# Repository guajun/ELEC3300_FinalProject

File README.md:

# ELEC3300_FinalProject

CAN - 电机

SDIO - sd卡

I2S - 扬声器

CRC 电机驱动信息校验

spi - oled ST7735

adc - 功率

uart - ws2812

uart - 3DConn 

usb hid - 键盘

uart - rs485（硬件流控）

Timer - encoder interface 增量编码器

Timer - PWM 呼吸灯

I2C - 距离传感器 VL53L0X

GPIO - Valve

GPIO - Relay

# ZYD

## 难
spi - oled ST7735

uart - 3DConn

## 一般
uart - ws2812

## 简单
Timer - encoder interface 增量编码器

## 超简单
Timer - PWM 呼吸灯

adc - 功率

GPIO - Valve

GPIO - Relay

# LGY
CAN - 电机

SDIO - sd卡

I2S - 扬声器

CRC 电机驱动信息校验

usb hid - 键盘

uart - rs485（硬件流控）

I2C - 距离传感器 VL53L0X

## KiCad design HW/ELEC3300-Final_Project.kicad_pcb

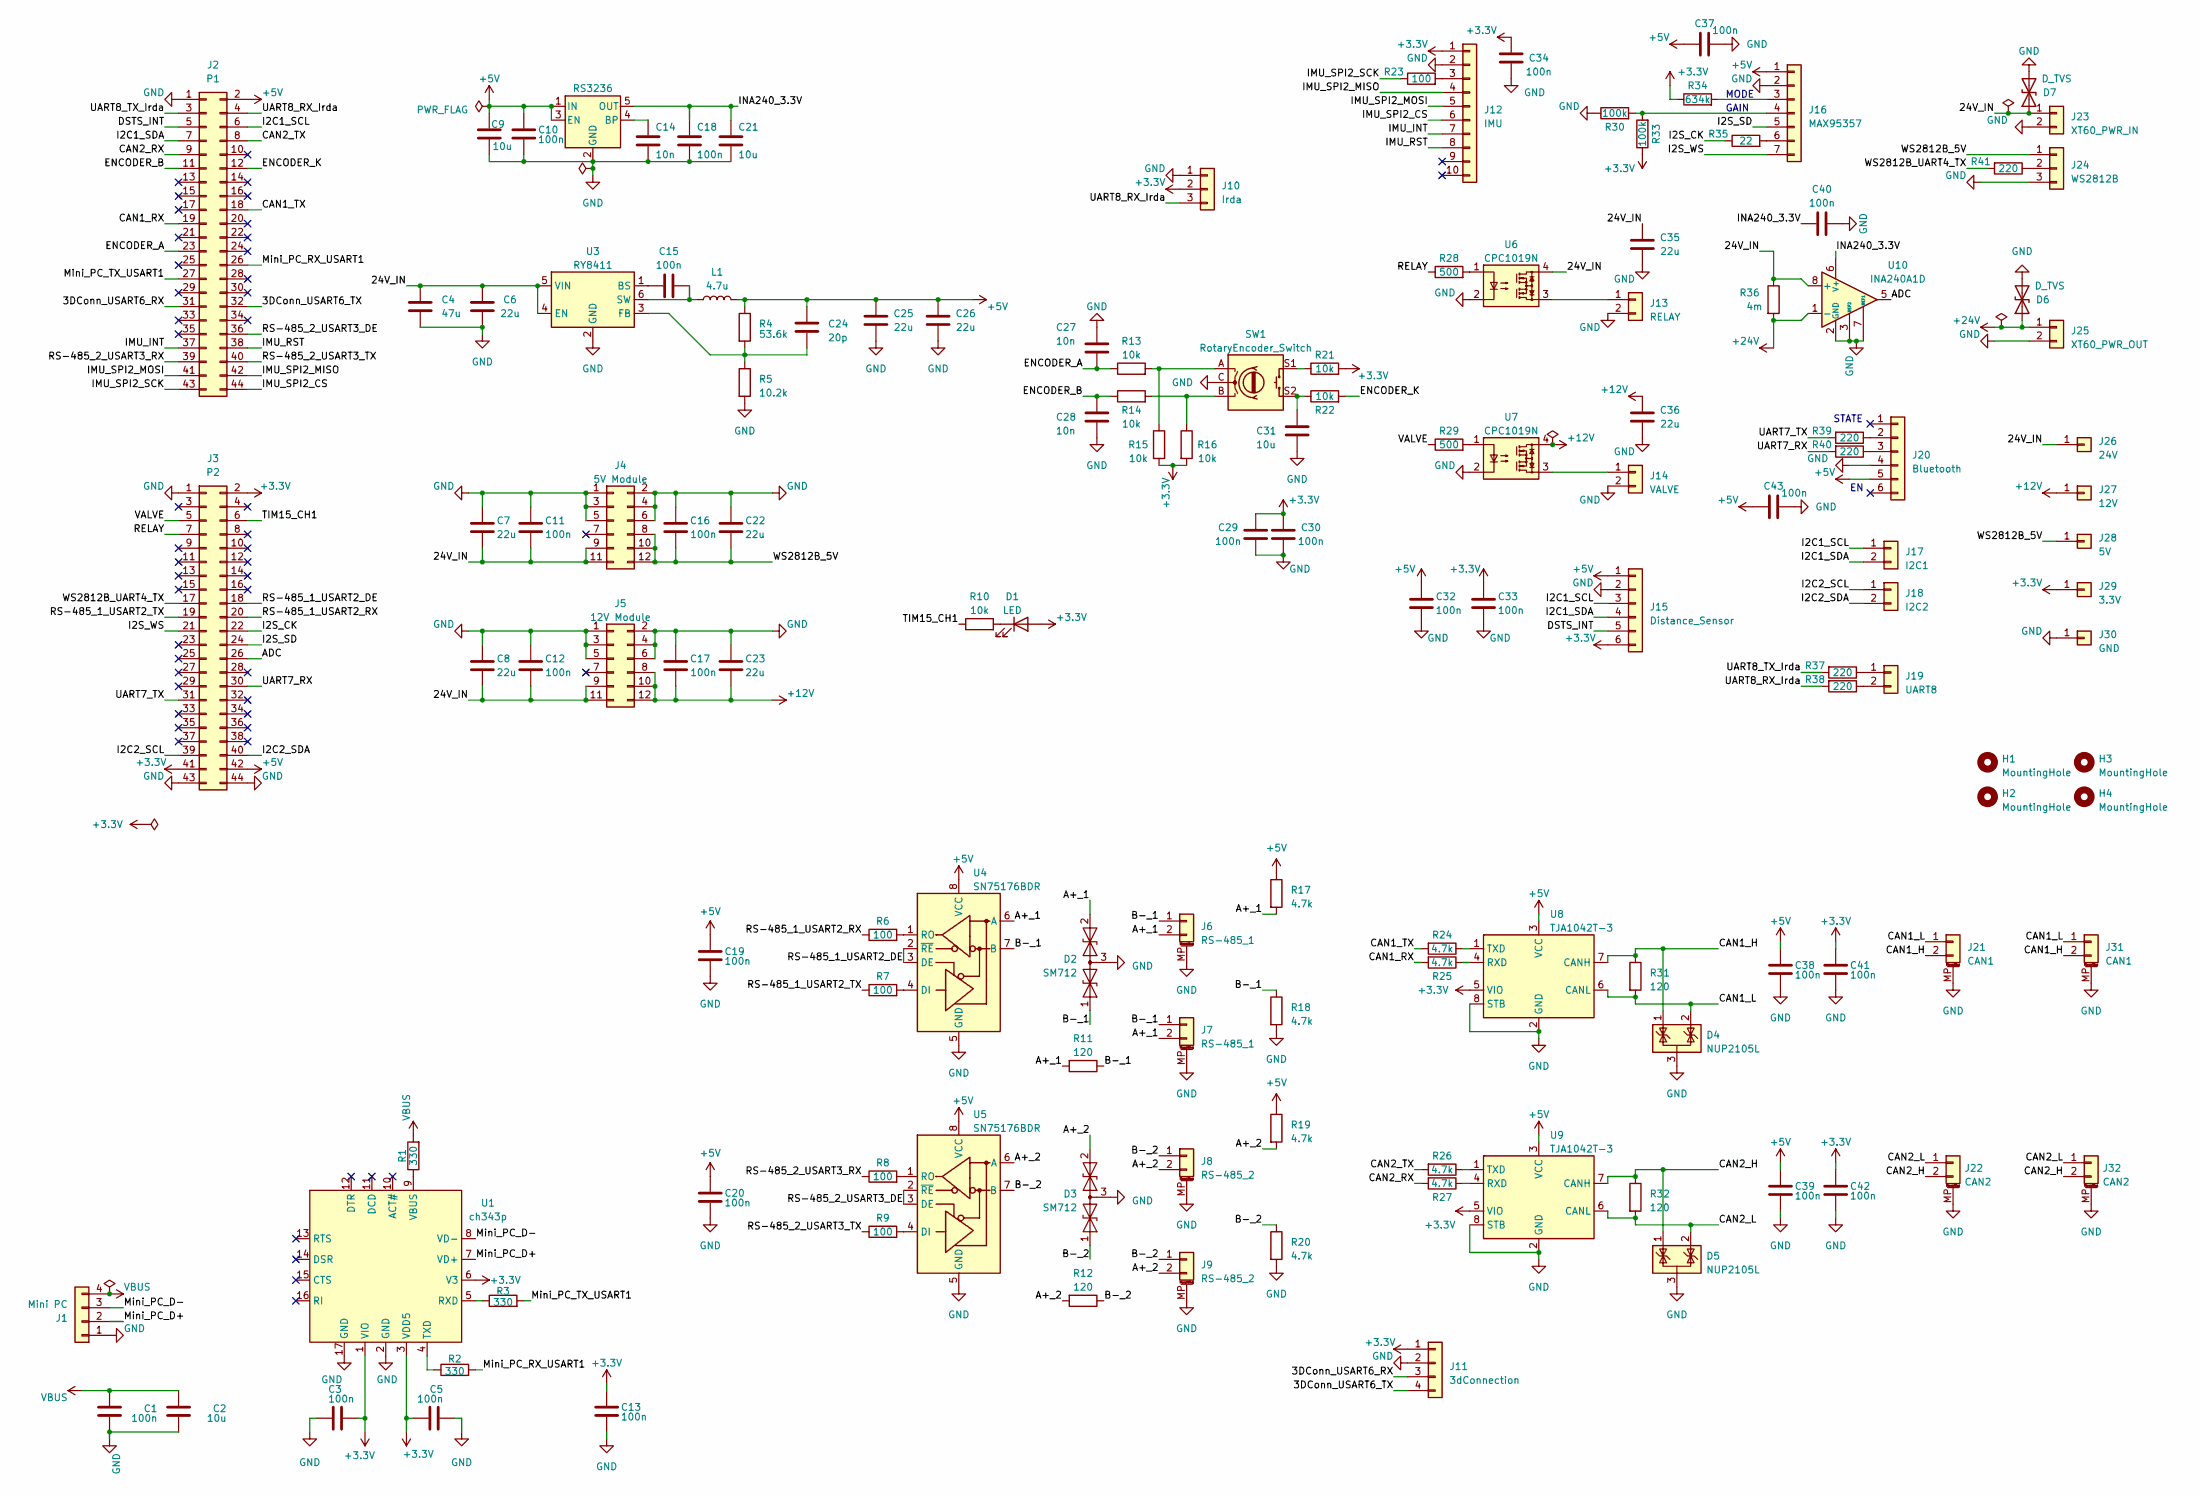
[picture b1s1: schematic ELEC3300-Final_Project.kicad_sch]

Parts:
C1, C3, C5, C10, C11, C12, C13, C15, C16, C17, C18, C19, C20, C29, C30, C32, C33, C34, C37, C38, C39, C40, C41, C42, C43: 100n; C_0603_1608Metric
C2, C9, C21: 10u; C_0805_2012Metric
C4: 47u; C_1206_3216Metric
C6, C7, C8, C22, C23, C25, C26, C35, C36: 22u; C_0805_2012Metric
C14, C27, C28: 10n; C_0603_1608Metric
C24: 20p; C_0603_1608Metric
C31: 10u; C_0603_1608Metric
D1: LED; LED_0603_1608Metric
D2, D3: SM712; SOT-23
D4, D5: NUP2105L; SOT-23
D6, D7: D_TVS; D_SMC
H1, H2, H3, H4: MountingHole; MountingHole_3.2mm_M3_ISO7380_Pad
J1: Mini PC; JST_PH_S4B-PH-K_1x04_P2.00mm_Horizontal
J2: P1; PinSocket_2x22_P2.54mm_Vertical
J3: P2; PinSocket_2x22_P2.54mm_Vertical
J4: 5V Module; 24V Buck
J5: 12V Module; 24V Buck
J6, J7: RS-485_1; JST_GH_SM02B-GHS-TB_1x02-1MP_P1.25mm_Horizontal
J8, J9: RS-485_2; JST_GH_SM02B-GHS-TB_1x02-1MP_P1.25mm_Horizontal
J10: Irda; PinSocket_1x03_P2.54mm_Vertical
J11: 3dConnection; PinHeader_1x04_P2.54mm_Horizontal
J12: IMU; PinSocket_1x10_P2.54mm_Vertical
J13: RELAY; JST_PH_S2B-PH-SM4-TB_1x02-1MP_P2.00mm_Horizontal
J14: VALVE; JST_PH_S2B-PH-SM4-TB_1x02-1MP_P2.00mm_Horizontal
J15: Distance_Sensor; PinSocket_1x06_P2.54mm_Horizontal
J16: MAX95357; PinSocket_1x07_P2.54mm_Vertical
J17: I2C1; PinHeader_1x02_P2.54mm_Vertical
J18: I2C2; PinHeader_1x02_P2.54mm_Vertical
J19: UART8; PinHeader_1x02_P2.54mm_Vertical
J20: Bluetooth; PinSocket_1x06_P2.54mm_Vertical
J21, J31: CAN1; JST_GH_SM02B-GHS-TB_1x02-1MP_P1.25mm_Horizontal
J22, J32: CAN2; JST_GH_SM02B-GHS-TB_1x02-1MP_P1.25mm_Horizontal
J23: XT60_PWR_IN; AMASS_XT60-M_1x02_P7.20mm_Vertical
J24: WS2812B; PinHeader_1x03_P2.54mm_Vertical
J25: XT60_PWR_OUT; AMASS_XT60-F_1x02_P7.20mm_Vertical
J26: 24V; TestPoint_Pad_4.0x4.0mm
J27: 12V; TestPoint_Pad_2.0x2.0mm
J28: 5V; TestPoint_Pad_2.0x2.0mm
J29: 3.3V; TestPoint_Pad_2.0x2.0mm
J30: GND; TestPoint_Pad_4.0x4.0mm
L1: 4.7u; L_Abracon_ASPI-0630LR
R1, R2, R3: 330; R_0603_1608Metric
R4: 53.6k; R_0603_1608Metric
R5: 10.2k; R_0603_1608Metric
R6, R7, R8, R9, R23: 100; R_0603_1608Metric
R10, R13, R14, R15, R16, R21, R22: 10k; R_0603_1608Metric
R11, R12, R31, R32: 120; R_0603_1608Metric
R17, R18, R19, R20, R24, R25, R26, R27: 4.7k; R_0603_1608Metric
R28, R29: 500; R_0603_1608Metric
R30, R33: 100k; R_0603_1608Metric
R34: 634k; R_0603_1608Metric
R35: 22; R_0603_1608Metric
R36: 4m; R_2512_6332Metric
R37, R38, R39, R40, R41: 220; R_0603_1608Metric
SW1: RotaryEncoder_Switch; RotaryEncoder_Alps_EC11E-Switch_Vertical_H20mm
U1: ch343p; CH343P
U2: RS3236; SOT-23-5
U3: RY8411; SOT-23-6
U4, U5: SN75176BDR; SOIC-8_3.9x4.9mm_P1.27mm
U6, U7: CPC1019N; SOP-4_3.8x4.1mm_P2.54mm
U8, U9: TJA1042T-3; SOIC-8_3.9x4.9mm_P1.27mm
U10: INA240A1D; SOIC-8_3.9x4.9mm_P1.27mm

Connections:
+3.3V: C3.1, C5.1, C13.1, C29.2, C30.2, C33.2, C34.2, C41.1, C42.1, D1.2 (A), J3.2, J3.41, J10.2, J11.1, J12.1, J15.6, J29.1, R15.2, R16.2, R21.2, R33.1, R34.1, U1.1 (VIO), U1.3 (VDD5), U1.6 (V3), U8.5 (VIO), U9.5 (VIO)
+5V: C9.1, C10.1, C19.1, C20.1, C24.1, C25.1, C26.1, C32.1, C37.1, C38.1, C39.1, C43.1, J2.2, J3.42, J15.1, J16.1, J20.5, L1.2, R4.1, R17.1, R19.1, U2.1 (IN), U2.3 (EN), U4.8 (VCC), U5.8 (VCC), U8.3 (VCC), U9.3 (VCC)
+12V: C17.2, C23.2, C36.1, J5.8, J5.10, J5.12, J27.1, U7.4
+24V: D6.1 (A1), J25.1, R36.2, U10.1 (-)
/3DConn_USART6_RX: J2.31, J11.3
/3DConn_USART6_TX: J2.32, J11.4
/24V_IN: C4.1, C6.1, C7.2, C8.2, C11.2, C12.2, C35.1, D7.1 (A1), J4.9, J4.11, J5.9, J5.11, J23.1, J26.1, R36.1, U3.4 (EN), U3.5 (VIN), U6.4, U10.8 (+)
/A+_1: D2.2 (A2), J6.2, J7.2, R11.2, R17.2, U4.6 (A)
/A+_2: D3.2 (A2), J8.2, J9.2, R12.2, R19.2, U5.6 (A)
/ADC: J3.26, U10.5
/B-_1: D2.1 (A1), J6.1, J7.1, R11.1, R18.1, U4.7 (B)
/B-_2: D3.1 (A1), J8.1, J9.1, R12.1, R20.1, U5.7 (B)
/CAN1_H: D4.1 (K), J21.2, J31.2, R31.1, U8.7 (CANH)
/CAN1_L: D4.2 (K), J21.1, J31.1, R31.2, U8.6 (CANL)
/CAN1_RX: J2.19, R25.2
/CAN1_TX: J2.18, R24.2
/CAN2_H: D5.1 (K), J22.2, J32.2, R32.1, U9.7 (CANH)
/CAN2_L: D5.2 (K), J22.1, J32.1, R32.2, U9.6 (CANL)
/CAN2_RX: J2.9, R27.2
/CAN2_TX: J2.8, R26.2
/DSTS_INT: J2.5, J15.5
/ENCODER_A: C27.2, J2.23, R13.1
/ENCODER_B: C28.1, J2.11, R14.1
/ENCODER_K: J2.12, R22.2
/I2C1_SCL: J2.6, J15.3, J17.1
/I2C1_SDA: J2.7, J15.4, J17.2
/I2C2_SCL: J3.39, J18.1
/I2C2_SDA: J3.40, J18.2
/I2S_CK: J3.22, R35.1
/I2S_SD: J3.24, J16.5
/I2S_WS: J3.21, J16.7
/IMU_INT: J2.37, J12.7
/IMU_RST: J2.38, J12.8
/IMU_SPI2_CS: J2.44, J12.6
/IMU_SPI2_MISO: J2.42, J12.4
/IMU_SPI2_MOSI: J2.41, J12.5
/IMU_SPI2_SCK: J2.43, R23.1
/INA240_3.3V: C18.1, C21.1, C40.1, U2.5 (OUT), U10.6 (V+)
/Mini_PC_D+: J1.2, U1.7 (VD+)
/Mini_PC_D-: J1.3, U1.8 (VD-)
/Mini_PC_RX_USART1: J2.26, R2.2
/Mini_PC_TX_USART1: J2.27, R3.2
/RELAY: J3.7, R28.1
/RS-485_1_USART2_DE: J3.18, U4.2 (~RE), U4.3 (DE)
/RS-485_1_USART2_RX: J3.20, R6.1
/RS-485_1_USART2_TX: J3.19, R7.1
/RS-485_2_USART3_DE: J2.36, U5.2 (~RE), U5.3 (DE)
/RS-485_2_USART3_RX: J2.39, R8.1
/RS-485_2_USART3_TX: J2.40, R9.1
/TIM15_CH1: J3.6, R10.1
/UART7_RX: J3.30, R40.2
/UART7_TX: J3.31, R39.2
/UART8_RX_Irda: J2.4, J10.3, R38.2
/UART8_TX_Irda: J2.3, R37.2
/VALVE: J3.5, R29.1
/WS2812B_5V: C16.2, C22.2, J4.8, J4.10, J4.12, J24.1, J28.1
/WS2812B_UART4_TX: J3.17, R41.2
GND: C1.2, C2.2, C3.2, C4.2, C5.2, C6.2, C7.1, C8.1, C9.2, C10.2, C11.1, C12.1, C13.2, C14.2, C16.1, C17.1, C18.2, C19.2, C20.2, C21.2, C22.1, C23.1, C25.2, C26.2, C27.1, C28.2, C29.1, C30.1, C31.2, C32.2, C33.1, C34.1, C35.2, C36.2, C37.2, C38.2, C39.2, C40.2, C41.2, C42.2, C43.2, D2.3 (common), D3.3 (common), D4.3 (A), D5.3 (A), D6.2 (A2), D7.2 (A2), J1.1, J2.1, J3.1, J3.43, J3.44, J4.1, J4.2, J4.3, J4.4, J4.5, J4.6, J5.1, J5.2, J5.3, J5.4, J5.5, J5.6, J6.MP (MountPin), J7.MP (MountPin), J8.MP (MountPin), J9.MP (MountPin), J10.1, J11.2, J12.2, J13.2, J14.2, J15.2, J16.2, J20.4, J21.MP (MountPin), J22.MP (MountPin), J23.2, J24.3, J25.2, J30.1, J31.MP (MountPin), J32.MP (MountPin), R5.2, R18.2, R20.2, R30.1, SW1.C, U1.2 (GND), U1.17 (GND), U2.2 (GND), U3.2 (GND), U4.5 (GND), U5.5 (GND), U6.2, U7.2, U8.2 (GND), U8.8 (STB), U9.2 (GND), U9.8 (STB), U10.2 (GND), U10.3 (REF2), U10.4 (GND), U10.7 (REF1)
unnamed: C31.1, R22.1, SW1.S2
unnamed: D1.1 (K), R10.2
unnamed: J12.3, R23.2
unnamed: J13.1, U6.3
unnamed: J14.1, U7.3
unnamed: J16.3, R34.2
unnamed: J16.4, R30.2, R33.2
unnamed: J16.6, R35.2
unnamed: J19.1, R37.1
unnamed: J19.2, R38.1
unnamed: J20.2, R39.1
unnamed: J20.3, R40.1
unnamed: J24.2, R41.1
unnamed: R13.2, R15.1, SW1.A
unnamed: R14.2, R16.1, SW1.B
unnamed: R21.1, SW1.S1
unnamed: R28.2, U6.1
unnamed: R29.2, U7.1
unnamed: R3.1, U1.5 (RXD)
unnamed: R2.1, U1.4 (TXD)
unnamed: R1.1, U1.9 (VBUS)
unnamed: C14.1, U2.4 (BP)
unnamed: C15.1, U3.1 (BS)
unnamed: C24.2, R4.2, R5.1, U3.3 (FB)
unnamed: C15.2, L1.1, U3.6 (SW)
unnamed: R7.2, U4.4 (DI)
unnamed: R6.2, U4.1 (RO)
unnamed: R9.2, U5.4 (DI)
unnamed: R8.2, U5.1 (RO)
unnamed: R25.1, U8.4 (RXD)
unnamed: R24.1, U8.1 (TXD)
unnamed: R27.1, U9.4 (RXD)
unnamed: R26.1, U9.1 (TXD)
VBUS: C1.1, C2.1, J1.4, R1.2

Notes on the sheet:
STATE
MODE
GAIN

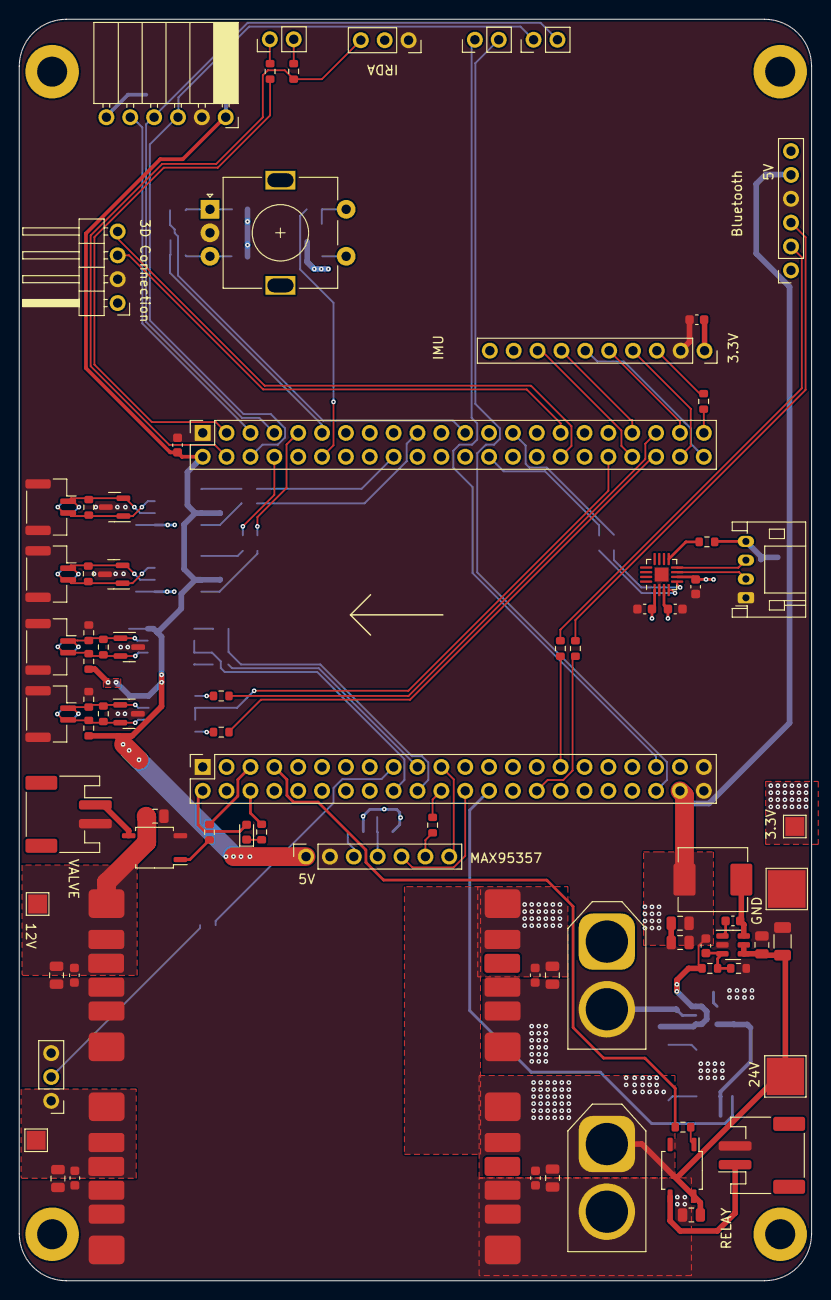
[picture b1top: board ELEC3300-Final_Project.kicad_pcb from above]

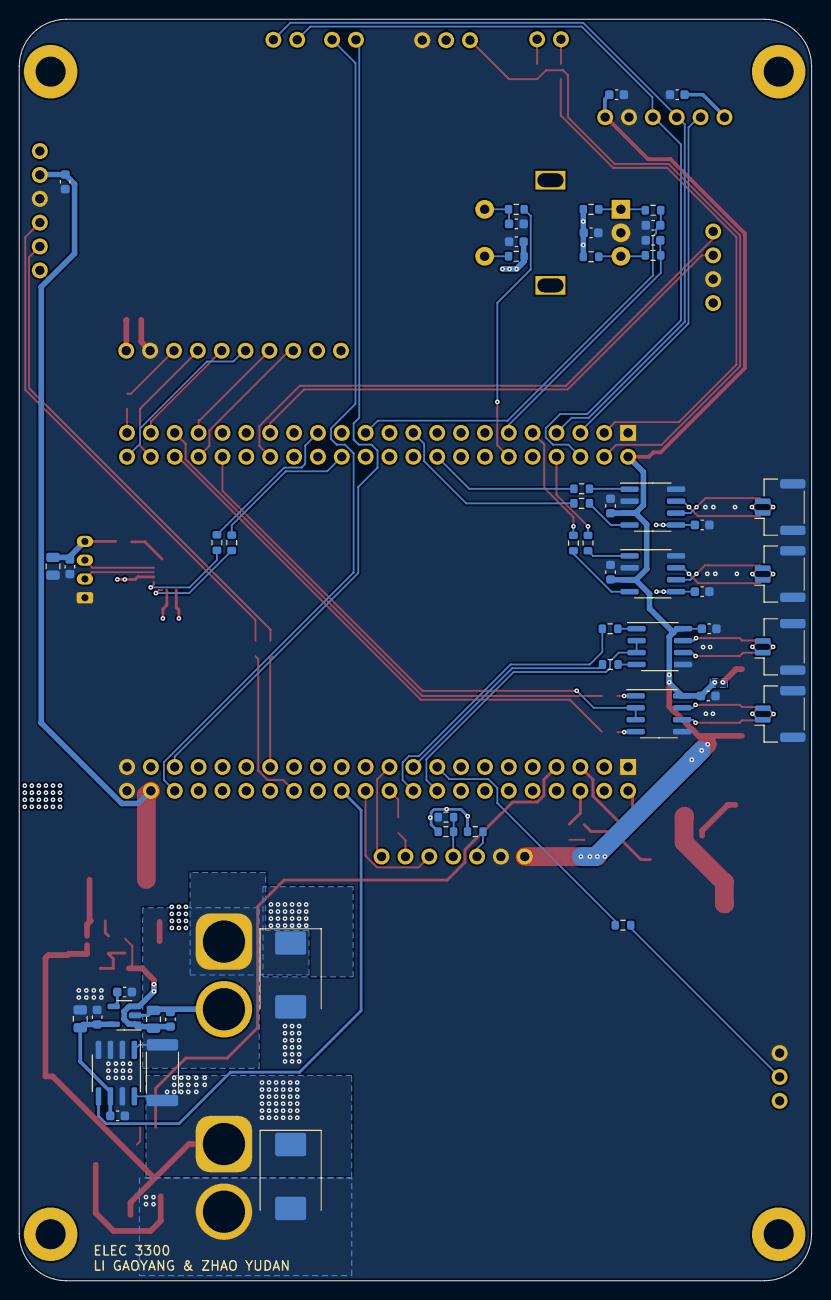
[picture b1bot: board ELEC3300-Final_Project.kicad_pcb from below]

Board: 4 copper layers, 84.3 x 134.3 mm, 139 parts (53 on the bottom side), 92 nets.

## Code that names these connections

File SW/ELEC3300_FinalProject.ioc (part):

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Mcu.Name=STM32H743VITx
Mcu.Package=LQFP100
Mcu.UserName=STM32H743VITx
PA0.GPIOParameters=GPIO_PuPd,GPIO_ModeDefaultOD
PA0.GPIO_ModeDefaultOD=GPIO_MODE_AF_PP
PA0.GPIO_PuPd=GPIO_NOPULL
PA0.Mode=Half_duplex(single_wire_mode)
PA0.Signal=UART4_TX
PA1.GPIOParameters=GPIO_PuPd
PA1.GPIO_PuPd=GPIO_PULLDOWN
PA1.Mode=Hardware Flow Control (RS485)
PA1.Signal=USART2_DE
PA10.Mode=Asynchronous
PA10.Signal=USART1_RX
PA11.Mode=Host_Only
PA11.Signal=USB_OTG_FS_DM
PA12.GPIOParameters=PinAttribute
PA12.Mode=Host_Only
PA12.PinAttribute=Free
PA12.Signal=USB_OTG_FS_DP
PA13\ (JTMS/SWDIO).Mode=Serial_Wire
PA13\ (JTMS/SWDIO).Signal=DEBUG_JTMS-SWDIO
PA14\ (JTCK/SWCLK).Mode=Serial_Wire
PA14\ (JTCK/SWCLK).Signal=DEBUG_JTCK-SWCLK
PA15\ (JTDI).GPIOParameters=PinAttribute
PA15\ (JTDI).PinAttribute=Free
PA15\ (JTDI).Signal=S_TIM2_CH1_ETR
PA2.GPIOParameters=GPIO_PuPd,PinAttribute
PA2.GPIO_PuPd=GPIO_PULLUP
PA2.Mode=Asynchronous
PA2.PinAttribute=Free
PA2.Signal=USART2_TX
PA3.GPIOParameters=GPIO_PuPd,PinAttribute
PA3.GPIO_PuPd=GPIO_PULLUP
PA3.Mode=Asynchronous
PA3.PinAttribute=Free
PA3.Signal=USART2_RX
PA4.GPIOParameters=PinAttribute
PA4.Mode=Half_Duplex_Master_Tx
PA4.PinAttribute=Free
PA4.Signal=I2S1_WS
PA5.Mode=Half_Duplex_Master_Tx
PA5.Signal=I2S1_CK
PA7.Mode=Half_Duplex_Master_Tx
PA7.Signal=I2S1_SDO
PA9.Mode=Asynchronous
PA9.Signal=USART1_TX
PB10.Mode=I2C
PB10.Signal=I2C2_SCL
PB11.Mode=I2C
PB11.Signal=I2C2_SDA
PB12.GPIOParameters=GPIO_PuPd
PB12.GPIO_PuPd=GPIO_PULLUP
PB12.Mode=NSS_Signal_Hard_Output
PB12.Signal=SPI2_NSS
PB13.GPIOParameters=GPIO_PuPd
PB13.GPIO_PuPd=GPIO_PULLUP
PB13.Mode=Full_Duplex_Master
PB13.Signal=SPI2_SCK
PB14.GPIOParameters=GPIO_PuPd,PinAttribute
PB14.GPIO_PuPd=GPIO_PULLUP
PB14.Mode=Full_Duplex_Master
PB14.PinAttribute=Free
PB14.Signal=SPI2_MISO
PB15.GPIOParameters=GPIO_PuPd,PinAttribute
PB15.GPIO_PuPd=GPIO_NOPULL
PB15.Mode=Full_Duplex_Master
PB15.PinAttribute=Free
PB15.Signal=SPI2_MOSI
PB3\ (JTDO/TRACESWO).GPIOParameters=PinAttribute
PB3\ (JTDO/TRACESWO).PinAttribute=Free
PB3\ (JTDO/TRACESWO).Signal=S_TIM2_CH2
PB5.GPIOParameters=PinAttribute
PB5.Mode=FDCAN_Activate
PB5.PinAttribute=Free
PB5.Signal=FDCAN2_RX
PB6.Mode=FDCAN_Activate
PB6.Signal=FDCAN2_TX
PB7.Signal=GPXTI7
PB8.GPIOParameters=PinAttribute
PB8.Mode=I2C
PB8.PinAttribute=Free
PB8.Signal=I2C1_SCL
PB9.GPIOParameters=PinAttribute
PB9.Mode=I2C
PB9.PinAttribute=Free
PB9.Signal=I2C1_SDA
PC0.GPIOParameters=GPIO_Label,PinAttribute
PC0.GPIO_Label=VBUS
PC0.PinAttribute=Free
PC0.Signal=GPIO_Output
PC10.Mode=SD_4_bits_Wide_bus
PC10.Signal=SDMMC1_D2
PC11.Mode=SD_4_bits_Wide_bus
PC11.Signal=SDMMC1_D3
PC12.GPIOParameters=GPIO_PuPd,PinAttribute
PC12.GPIO_PuPd=GPIO_PULLUP
PC12.Mode=SD_4_bits_Wide_bus
PC12.PinAttribute=Free
PC12.Signal=SDMMC1_CK
PC13.GPIOParameters=GPIO_Label
PC13.GPIO_Label=K1
PC13.Signal=GPIO_Input
PC5.Signal=ADCx_INP8
PC6.GPIOParameters=GPIO_PuPd
PC6.GPIO_PuPd=GPIO_PULLUP
PC6.Mode=Asynchronous
PC6.Signal=USART6_TX
PC7.GPIOParameters=GPIO_PuPd
PC7.GPIO_PuPd=GPIO_PULLUP
PC7.Mode=Asynchronous
PC7.Signal=USART6_RX
PC8.Mode=SD_4_bits_Wide_bus
PC8.Signal=SDMMC1_D0
PC9.Mode=SD_4_bits_Wide_bus
PC9.Signal=SDMMC1_D1
PD0.GPIOParameters=PinAttribute
PD0.Mode=FDCAN_Activate
PD0.PinAttribute=Free
PD0.Signal=FDCAN1_RX
PD1.GPIOParameters=PinAttribute
PD1.Mode=FDCAN_Activate
PD1.PinAttribute=Free
PD1.Signal=FDCAN1_TX
PD10.GPIOParameters=GPIO_PuPd,GPIO_Label
PD10.GPIO_Label=IMU_RST
PD10.GPIO_PuPd=GPIO_PULLDOWN
PD10.Signal=GPIO_Output
PD11.GPIOParameters=GPIO_PuPd,GPIO_Label,GPIO_ModeDefaultEXTI
PD11.GPIO_Label=IMU_INT
PD11.GPIO_ModeDefaultEXTI=GPIO_MODE_IT_FALLING
PD11.GPIO_PuPd=GPIO_PULLUP
PD11.Signal=GPXTI11
PD12.Mode=Hardware Flow Control (RS485)
PD12.Signal=USART3_DE
PD2.GPIOParameters=PinAttribute
PD2.Mode=SD_4_bits_Wide_bus
PD2.PinAttribute=Free
PD2.Signal=SDMMC1_CMD
PD4.GPIOParameters=GPIO_PuPd,GPIO_Label,PinAttribute
PD4.GPIO_Label=SD_DET
PD4.GPIO_PuPd=GPIO_PULLDOWN
PD4.PinAttribute=Free
PD4.Signal=GPIO_Input
PD7.GPIOParameters=GPIO_Label,PinAttribute
PD7.GPIO_Label=ENCODER_K
PD7.PinAttribute=Free
PD7.Signal=GPIO_Input
PD8.Mode=Asynchronous
PD8.Signal=USART3_TX
PD9.Mode=Asynchronous
PD9.Signal=USART3_RX
PE0.Mode=IrDA
PE0.Signal=UART8_RX
PE1.Mode=IrDA
PE1.Signal=UART8_TX
PE10.Mode=PWM Generation2 CH2N
PE10.Signal=TIM1_CH2N
PE11.Mode=NSS_Signal_Hard_Output
PE11.Signal=SPI4_NSS
PE12.Mode=TX_Only_Simplex_Unidirect_Master
PE12.Signal=SPI4_SCK
PE13.GPIOParameters=GPIO_Label
PE13.GPIO_Label=LCD_WR_RS
PE13.Signal=GPIO_Output
PE14.Mode=TX_Only_Simplex_Unidirect_Master
PE14.Signal=SPI4_MOSI
PE3.GPIOParameters=GPIO_Label
PE3.GPIO_Label=LED
PE3.Signal=GPIO_Output
PE4.GPIOParameters=GPIO_Label
PE4.GPIO_Label=VALVE
PE4.Signal=GPIO_Output
PE5.Signal=S_TIM15_CH1
PE6.GPIOParameters=GPIO_Label
PE6.GPIO_Label=RELAY
PE6.Signal=GPIO_Output
PE7.Mode=Asynchronous
PE7.Signal=UART7_RX
PE8.Mode=Asynchronous
PE8.Signal=UART7_TX
PH0-OSC_IN\ (PH0).Mode=HSE-External-Oscillator
PH0-OSC_IN\ (PH0).Signal=RCC_OSC_IN
PH1-OSC_OUT\ (PH1).GPIOParameters=PinAttribute
PH1-OSC_OUT\ (PH1).Mode=HSE-External-Oscillator
PH1-OSC_OUT\ (PH1).PinAttribute=Free
PH1-OSC_OUT\ (PH1).Signal=RCC_OSC_OUT
RCC.SYSCLKFreq_VALUE=480000000
RCC.SYSCLKSource=RCC_SYSCLKSOURCE_PLLCLK
board=custom

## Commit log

2023-02-21 init
2023-02-21 add ignore
2023-04-12 remove ioc
2023-04-12 add readme
2023-04-12 add ioc
2023-04-12 gen code
2023-04-16 ignore HW files
2023-04-16 add dma
2023-04-16 ignore HW
2023-04-16 update gened files
2023-04-16 add module compile
2023-04-18 remove sd card test
2023-04-18 successfully read keyboard data
2023-04-18 config 3dConn uart
2023-04-18 init test
2023-04-18 rm st card tests
2023-04-18 Create module, add interruput enable callback register
2023-04-18 rm include
2023-04-18 creat module, modified timer config
2023-04-18 create feature_RotaryEncoder
2023-04-18 modified RotaryEncoder.c
2023-04-18 modified main.c
2023-04-18 add test, but fail
2023-04-18 remove SD card
2023-04-18 add IMU peripherals
2023-04-18 finish reading can be used for demo, need refining
2023-04-18 add 2812
2023-04-18 create feature_TemperatureSensor
2023-04-18 modified ThreeDConn, regenerate code
2023-04-19 add functions
2023-04-19 fix include
2023-04-24 finish sdio write, fix bug of i2s
2023-04-24 disable warning
2023-04-25 finish. Remember to check voltage supply value
2023-04-25 update ioc , change file name
2023-04-25 pass compile
2023-04-25 Finish
2023-04-25 finish BreathingLight and blink
2023-04-25 finish convert, need to add DMA
2023-04-25 fix DMA
2023-04-25 rm test
2023-04-26 finish config for 200Mhz DMA sdcard. update influenced clk
2023-04-27 remove file system
2023-04-27 successfully play
2023-04-27 finish DMA double buffer
2023-04-27 remove fatfs
2023-04-27 remove play
2023-05-05 rm sdcard
2023-05-05 add unitree CRC, update cubemx and firmware
2023-05-05 add data section
2023-05-06 not test
2023-05-06 finish lcd, no DMA
2023-05-06 fix declare
2023-05-07 finish all HT
2023-05-07 finish all HT DM
2023-05-07 Finish Unitree
2023-05-07 wait for test
2023-05-07 finish 2812 encoder
2023-05-07 try keyboard
2023-05-07 finish kb interface
2023-05-07 rm comments
2023-05-08 finish encoder adjust speed
2023-05-08 finish IMU ctrl
2023-05-08 temperature
2023-05-12 add delay before init
